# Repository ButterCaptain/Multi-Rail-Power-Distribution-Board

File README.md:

# Power Board 6 - Multi-Rail DC-DC Converter Board

A flexible power distribution board featuring three cascading buck converter stages for rapid prototyping and R&D testing.

## Overview

While working at Sable Systems International, I needed a way to quickly access multiple voltage rails during R&D testing without constantly rewiring power supplies. This board was developed to solve that problem by providing regulated outputs at different voltage levels from a single input source.

## Features

- **Primary Stage**: 24VDC → 12VDC buck converter
- **Secondary Stage**: 12VDC → 5VDC buck converter  
- **Tertiary Stage**: 5VDC → 3.3VDC buck converter
- High-efficiency power delivery optimized for multiple simultaneous loads
- Integrated protection and filtering on each rail

## Design

The board is designed in KiCAD and includes:
- Full schematic and PCB layout
- Custom component footprints and symbol libraries
- Thermal and power analysis documentation
- 3D model for visualization and assembly planning

## Files

- `Power_Board_6.kicad_sch` - Complete schematic
- `Power_Board_6.kicad_pcb` - PCB layout and routing
- `Power_Board_6.kicad_pro` - Project configuration and design rules
- `3D_Model.glb` - 3D visualization
- `Reports/` - Power analysis and design documentation

## Getting Started

To work with this design:
1. Install [KiCAD 10.0](https://www.kicad.org/download/) or compatible version
2. Open `Power_Board_6.kicad_pro` to view the complete project
3. Review power analysis reports in the `Reports/` directory before modifying converter stages

## Use Cases

- Rapid prototyping with devices requiring multiple voltage rails
- R&D testing platforms needing flexible power distribution
- Educational demonstrations of buck converter design
- Reference design for multi-stage power delivery systems

---

*Developed for efficient power distribution during research and development work.*

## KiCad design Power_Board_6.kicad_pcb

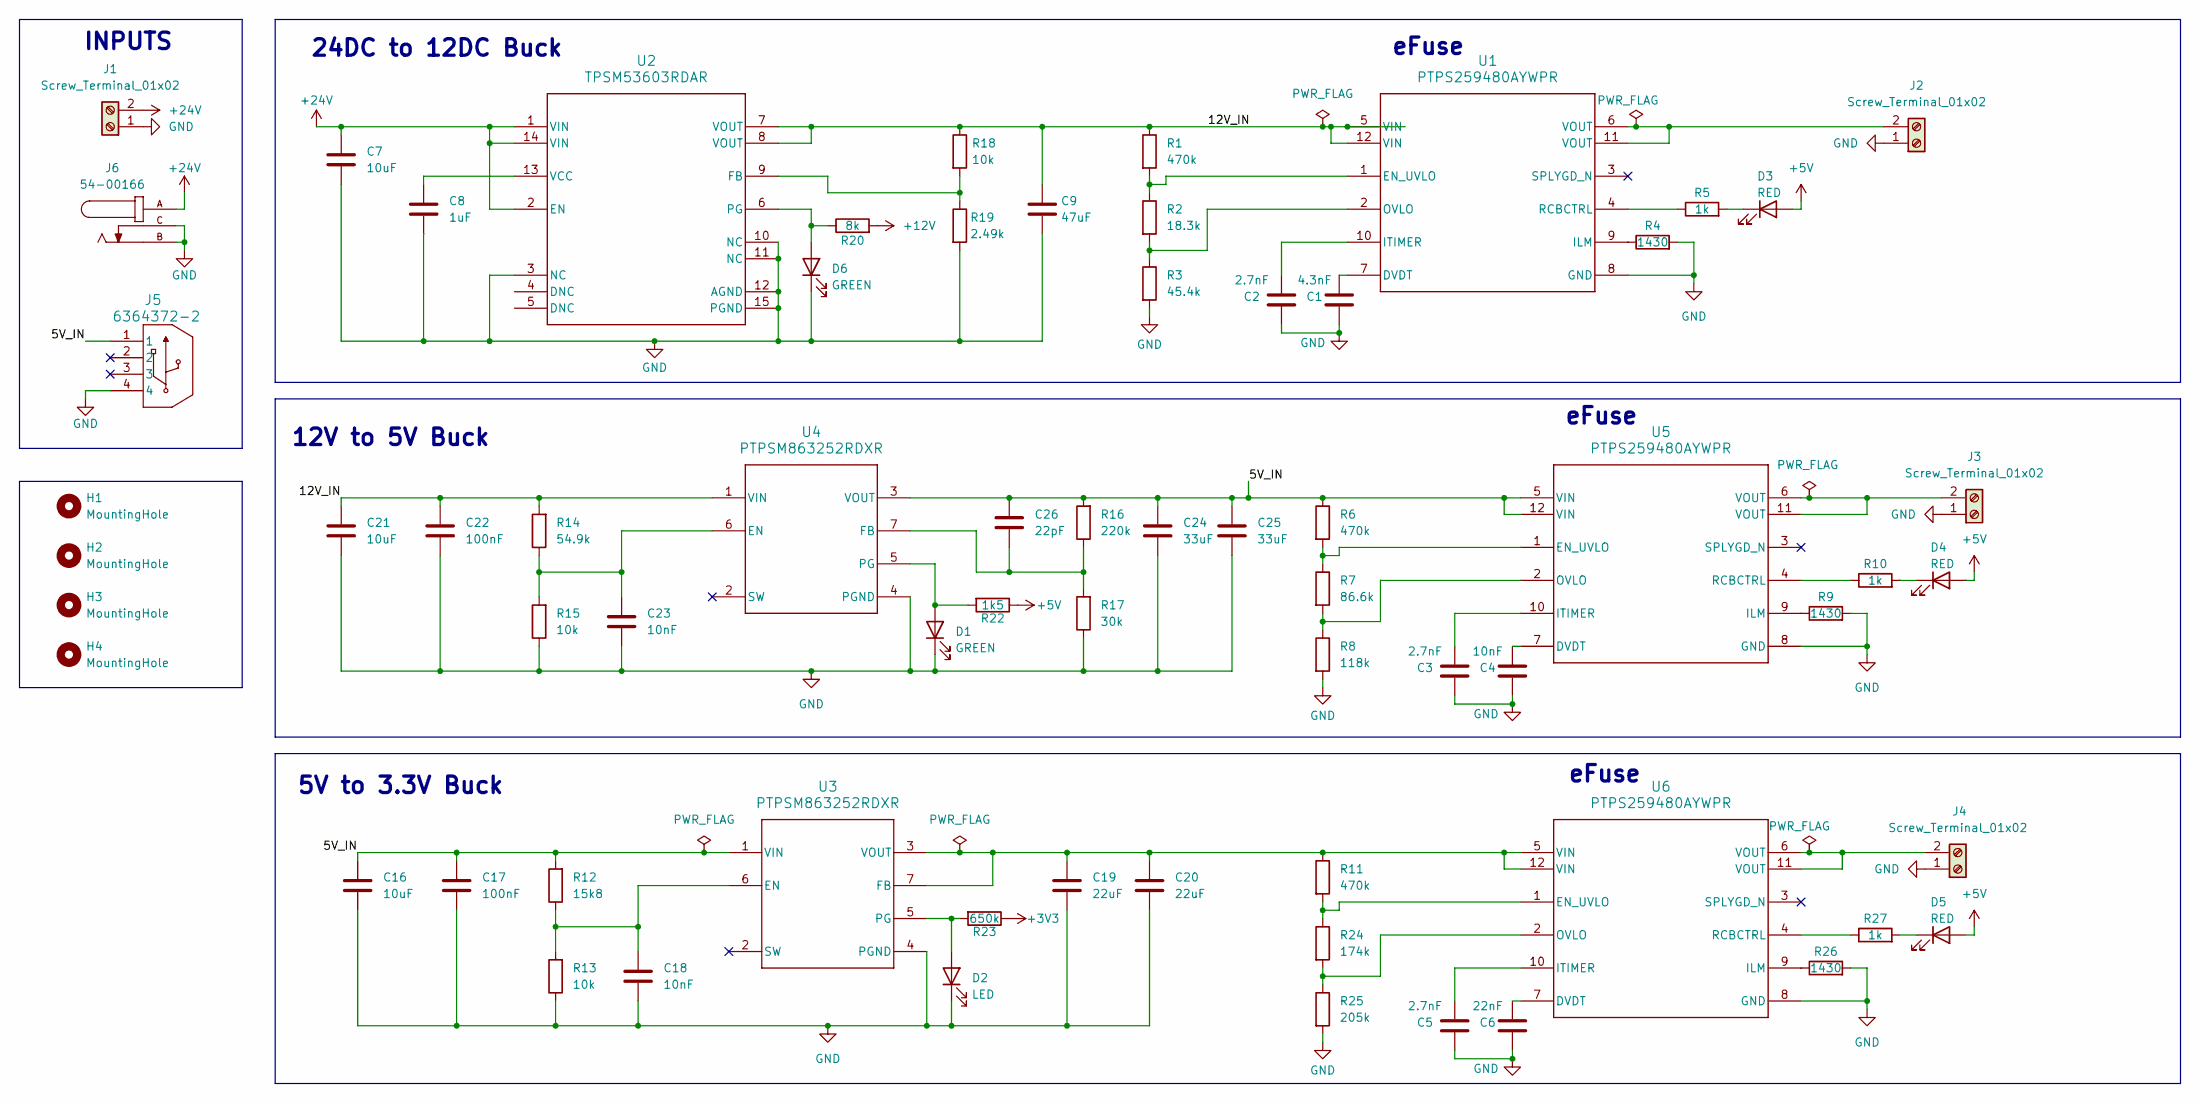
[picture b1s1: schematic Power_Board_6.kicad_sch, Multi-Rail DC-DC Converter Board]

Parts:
C1: 4.3nF; C_0805_2012Metric_Pad1.18x1.45mm_HandSolder
C2, C3, C5: 2.7nF; C_0805_2012Metric_Pad1.18x1.45mm_HandSolder
C4: 10nF; C_0805_2012Metric_Pad1.18x1.45mm_HandSolder
C6: 22nF; C_0805_2012Metric_Pad1.18x1.45mm_HandSolder
C7: 10uF; C_0805_2012Metric_Pad1.18x1.45mm_HandSolder
C8: 1uF; C_0805_2012Metric_Pad1.18x1.45mm_HandSolder
C9: 47uF; C_0805_2012Metric_Pad1.18x1.45mm_HandSolder
C16, C21: 10uF; R_0805_2012Metric_Pad1.20x1.40mm_HandSolder
C17, C22: 100nF; R_0805_2012Metric_Pad1.20x1.40mm_HandSolder
C18: 10nF; C_0603_1608Metric_Pad1.08x0.95mm_HandSolder
C19, C20: 22uF; R_0805_2012Metric_Pad1.20x1.40mm_HandSolder
C23: 10nF; R_0603_1608Metric_Pad0.98x0.95mm_HandSolder
C24, C25: 33uF; R_0805_2012Metric_Pad1.20x1.40mm_HandSolder
C26: 22pF; R_0805_2012Metric_Pad1.20x1.40mm_HandSolder
D1, D6: GREEN; LED_0603_1608Metric_Pad1.05x0.95mm_HandSolder
D2: LED; LED_0603_1608Metric_Pad1.05x0.95mm_HandSolder
D3, D4, D5: RED; LED_0603_1608Metric_Pad1.05x0.95mm_HandSolder
H1, H2, H3, H4: MountingHole; MountingHole_3.2mm_M3
J1, J2, J3, J4: Screw_Terminal_01x02; TerminalBlock_Phoenix_PT-1,5-2-5.0-H_1x02_P5.00mm_Horizontal
J5: 6364372-2; CONN_6364372-2_TEC
J6: 54-00166; TENSILITY_54-00166; PARTREV A
R1, R6, R11: 470k; R_0805_2012Metric_Pad1.20x1.40mm_HandSolder
R2: 18.3k; R_0805_2012Metric_Pad1.20x1.40mm_HandSolder
R3: 45.4k; R_0805_2012Metric_Pad1.20x1.40mm_HandSolder
R4, R9, R26: 1430; R_0805_2012Metric_Pad1.20x1.40mm_HandSolder
R5, R10, R27: 1k; R_0805_2012Metric_Pad1.20x1.40mm_HandSolder
R7: 86.6k; R_0805_2012Metric_Pad1.20x1.40mm_HandSolder
R8: 118k; R_0805_2012Metric_Pad1.20x1.40mm_HandSolder
R12: 15k8; R_0603_1608Metric_Pad0.98x0.95mm_HandSolder
R13, R15: 10k; R_0603_1608Metric_Pad0.98x0.95mm_HandSolder
R14: 54.9k; R_0603_1608Metric_Pad0.98x0.95mm_HandSolder
R16: 220k; R_0603_1608Metric_Pad0.98x0.95mm_HandSolder
R17: 30k; R_0603_1608Metric_Pad0.98x0.95mm_HandSolder
R18: 10k; R_0805_2012Metric_Pad1.20x1.40mm_HandSolder
R19: 2.49k; R_0805_2012Metric_Pad1.20x1.40mm_HandSolder
R20: 8k; R_0805_2012Metric_Pad1.20x1.40mm_HandSolder
R22: 1k5; R_0603_1608Metric_Pad0.98x0.95mm_HandSolder
R23: 650k; R_0603_1608Metric_Pad0.98x0.95mm_HandSolder
R24: 174k; R_0805_2012Metric_Pad1.20x1.40mm_HandSolder
R25: 205k; R_0805_2012Metric_Pad1.20x1.40mm_HandSolder
U1, U5, U6: PTPS259480AYWPR; YWP0012A-MFG
U2: TPSM53603RDAR; RDA0015A
U3, U4: PTPSM863252RDXR; RDX0007A-MFG_NOVIA

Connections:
+12V: R20.2
+24V: C7.1, J1.2, J6.A, U2.1 (VIN), U2.2 (EN), U2.14 (VIN)
/5V_IN: C16.1, C17.1, C24.1, C25.1, C26.1, J5.1, R6.1, R12.2, R16.2, U3.1 (VIN), U4.3 (VOUT), U5.5 (VIN), U5.12 (VIN)
/12V_IN: C9.1, C21.1, C22.1, R1.1, R14.2, R18.1, U1.5 (VIN), U1.12 (VIN), U2.7 (VOUT), U2.8 (VOUT), U4.1 (VIN)
GND: C1.1, C2.1, C3.1, C4.1, C5.1, C6.1, C7.2, C8.2, C9.2, C16.2, C17.2, C18.2, C19.2, C20.2, C21.2, C22.2, C23.2, C24.2, C25.2, D1.1 (K), D2.1 (K), D6.1 (K), J1.1, J2.1, J3.1, J4.1, J5.4, J6.B, J6.C, R3.2, R4.2, R8.2, R9.2, R13.1, R15.1, R17.1, R19.2, R25.2, R26.2, U1.8 (GND), U2.3 (NC), U2.10 (NC), U2.11 (NC), U2.12 (AGND), U2.15 (PGND), U3.4 (PGND), U4.4 (PGND), U5.8 (GND), U6.8 (GND)
unnamed: D1.2 (A), R22.2, U4.5 (PG)
unnamed: D2.2 (A), R23.2, U3.5 (PG)
unnamed: D3.1 (K), R5.2
unnamed: D4.1 (K), R10.2
unnamed: D5.1 (K), R27.2
unnamed: D6.2 (A), R20.1, U2.6 (PG)
unnamed: J2.2, U1.6 (VOUT), U1.11 (VOUT)
unnamed: C1.2, U1.7 (DVDT)
unnamed: R1.2, R2.1, U1.1 (EN_UVLO)
unnamed: R4.1, U1.9 (ILM)
unnamed: C2.2, U1.10 (ITIMER)
unnamed: R2.2, R3.1, U1.2 (OVLO)
unnamed: R5.1, U1.4 (RCBCTRL)
unnamed: R18.2, R19.1, U2.9 (FB)
unnamed: C8.1, U2.13 (VCC)
unnamed: C18.1, R12.1, R13.2, U3.6 (EN)
unnamed: C19.1, C20.1, R11.1, U3.3 (VOUT), U3.7 (FB), U6.5 (VIN), U6.12 (VIN)
unnamed: C23.1, R14.1, R15.2, U4.6 (EN)
unnamed: C26.2, R16.1, R17.2, U4.7 (FB)
unnamed: C4.2, U5.7 (DVDT)
unnamed: R6.2, R7.1, U5.1 (EN_UVLO)
unnamed: R9.1, U5.9 (ILM)
unnamed: C3.2, U5.10 (ITIMER)
unnamed: R7.2, R8.1, U5.2 (OVLO)
unnamed: R10.1, U5.4 (RCBCTRL)
unnamed: C6.2, U6.7 (DVDT)
unnamed: R11.2, R24.1, U6.1 (EN_UVLO)
unnamed: R26.1, U6.9 (ILM)
unnamed: C5.2, U6.10 (ITIMER)
unnamed: R24.2, R25.1, U6.2 (OVLO)
unnamed: R27.1, U6.4 (RCBCTRL)

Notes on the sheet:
24DC to 12DC Buck
eFuse
INPUTS
12V to 5V Buck
5V to 3.3V Buck

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
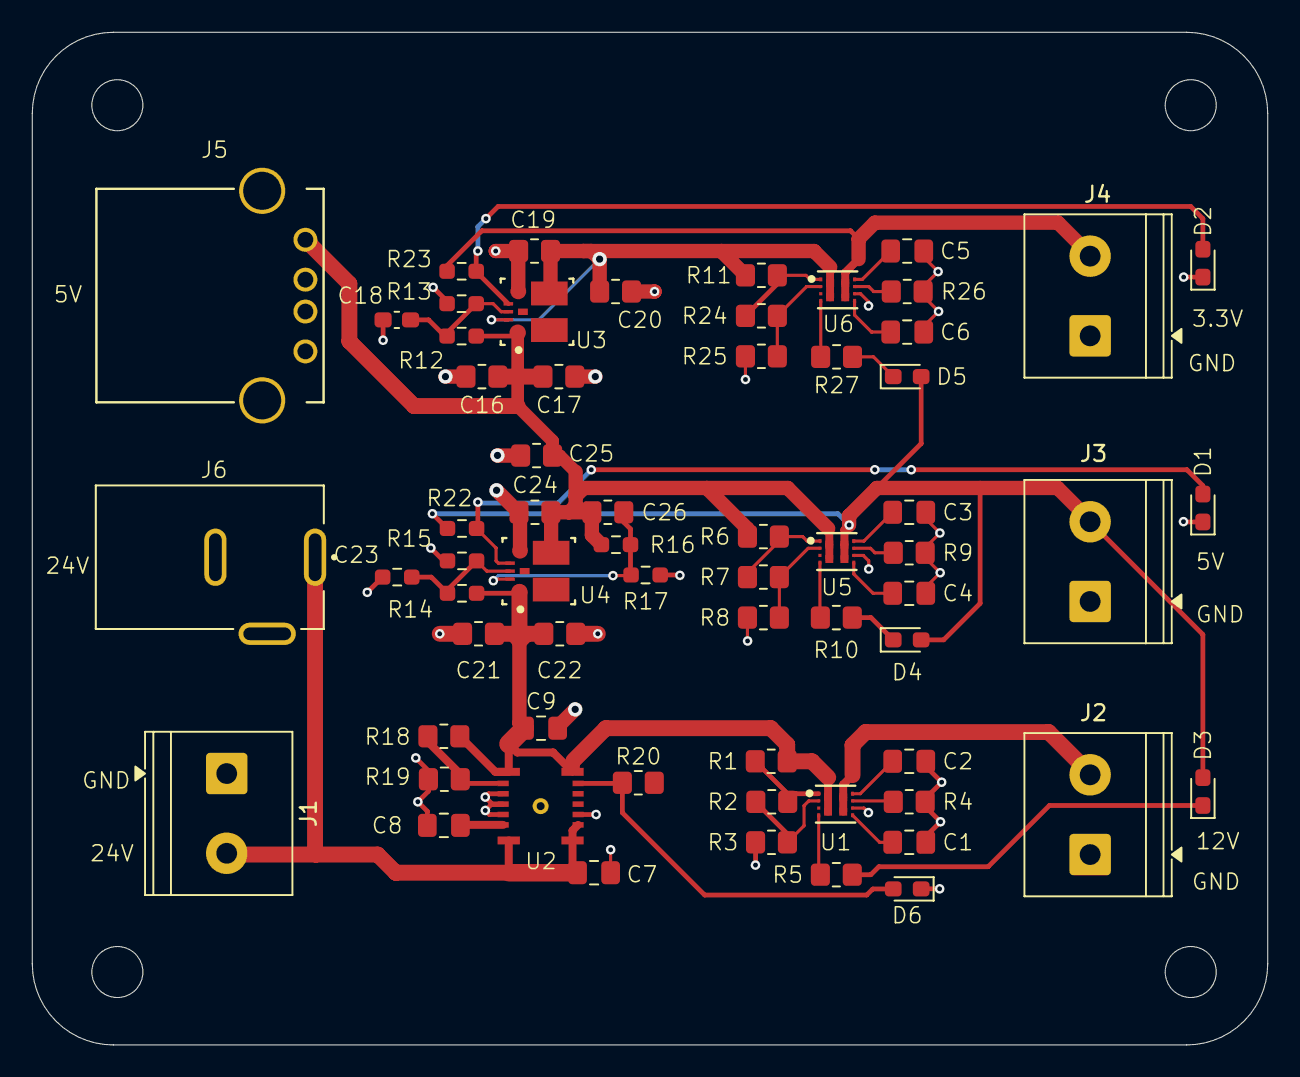
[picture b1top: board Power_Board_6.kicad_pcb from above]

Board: 2 copper layers, 77.5 x 63.5 mm, 68 parts (0 on the bottom side), 37 nets.
